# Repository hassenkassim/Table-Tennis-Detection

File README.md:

# Table-Tennis-Detection

> This project is about a detecting the impact position of table tennis ball on the racket by using 3 Piezo vibration sensors fixed to a table tennis racket and a custom designed microcontroller circuit (EMF32 GG).

## Note

The data model cannot be published. Nevertheless the mechanics is apparent.

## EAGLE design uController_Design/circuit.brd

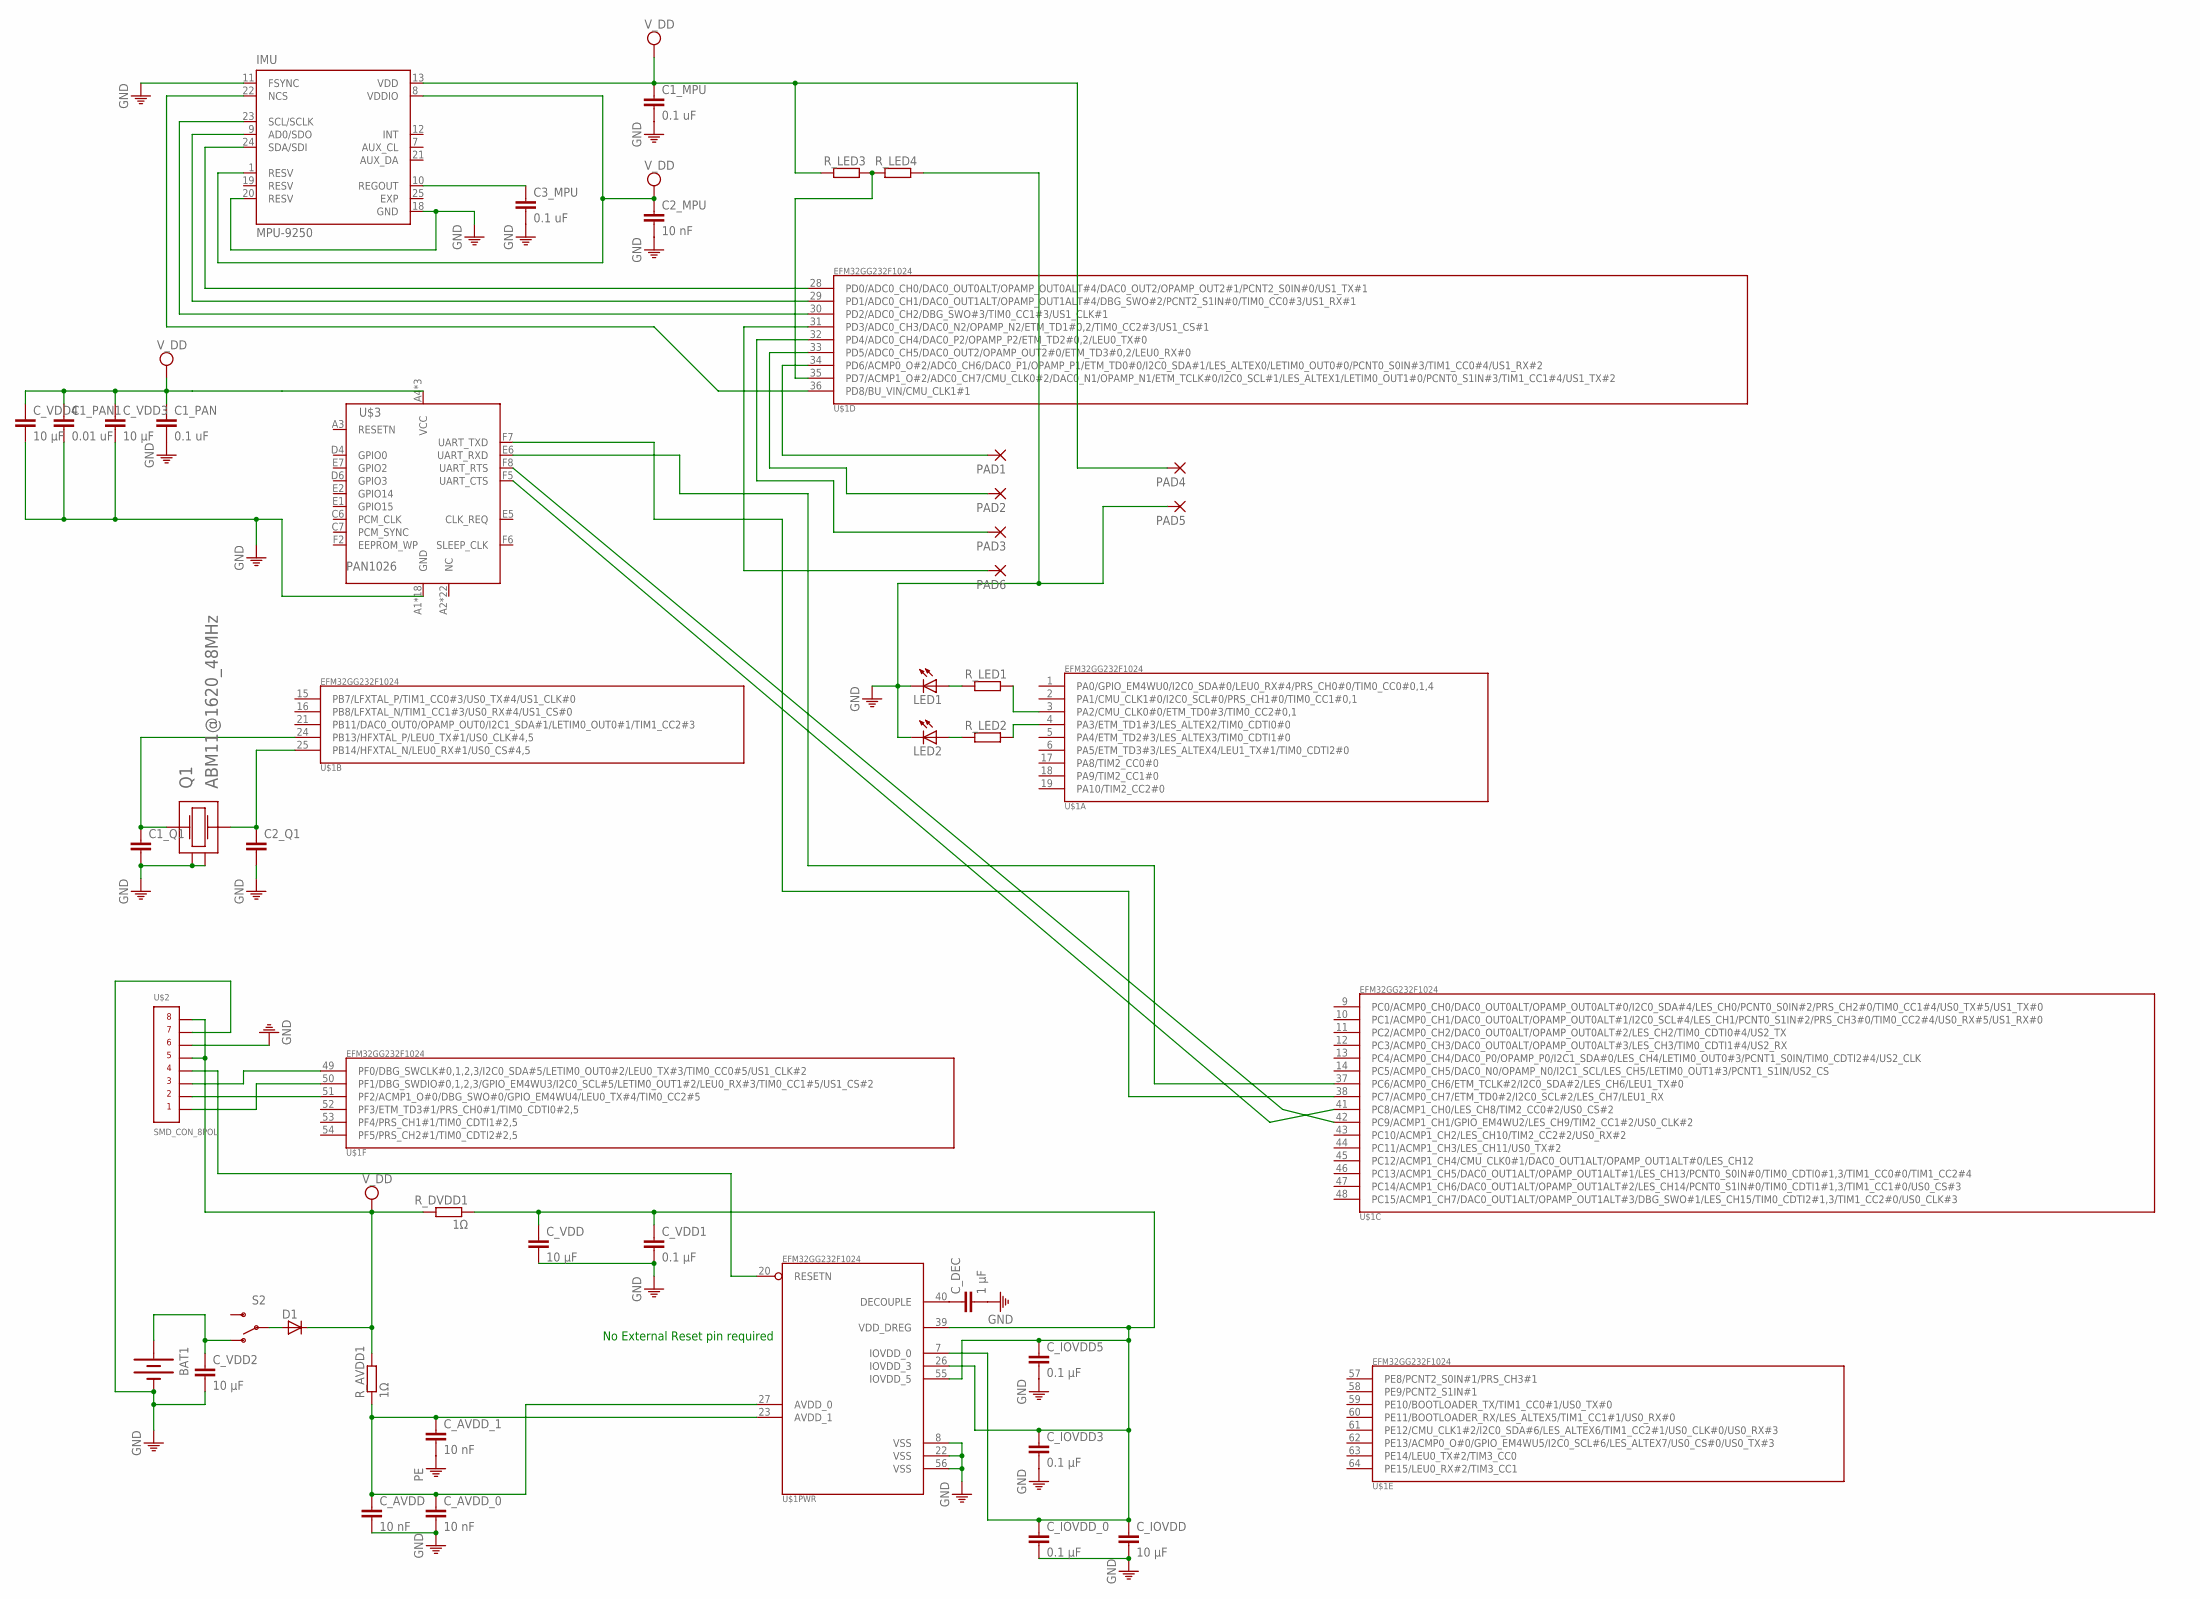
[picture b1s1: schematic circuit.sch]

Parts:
BAT1: BATTERY20MM_4LEGS_OVERPASTE; BATTCON_20MM_4LEGS_OVERPASTE
C1_MPU, C1_PAN, C3_MPU: 0.1 uF; C0603
C1_PAN1: 0.01 uF; C0603
C1_Q1, C2_Q1: C-EUC0603; C0603
C2_MPU: 10 nF; C0603
C_AVDD: 10 nF; C0603
C_AVDD_0, C_AVDD_1: 10 nF; C0603
C_DEC: 1 µF; C0603
C_IOVDD: 10 µF; C0805
C_IOVDD3, C_IOVDD5: 0.1 µF; C0603
C_IOVDD_0: 0.1 µF; C0603
C_VDD, C_VDD2, C_VDD3, C_VDD4: 10 µF; C0805
C_VDD1: 0.1 µF; C0603
D1: D-SOD123; SOD123
IMU: MPU-9250; QFN40P300X300X105-25N
LED1, LED2: LEDCHIPLED_0805; CHIPLED_0805
PAD1, PAD2, PAD3, PAD4, PAD5, PAD6: SMD2; SMD1,27-2,54
Q1: ABM11@1620_48MHz; 1620
R_AVDD1: 1Ω; R0603
R_DVDD1: 1Ω; R0603
R_LED1, R_LED2, R_LED3, R_LED4: R-EU_R0603; R0603
S2: SWITCH-SPDTSMD2; SWITCH-SPDT-SMD
U$1: EFM32GG232F1024; QFP64
U$2: SMD_CON_8POL
U$3: PAN1026

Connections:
EXP: IMU.25 (EXP)
GND: BAT1.2 (-), C1_MPU.2, C1_PAN.2, C1_PAN1.2, C1_Q1.2, C2_MPU.2, C2_Q1.2, C3_MPU.2, C_AVDD.2, C_AVDD_0.2, C_AVDD_1.2, C_DEC.2, C_IOVDD.2, C_IOVDD3.2, C_IOVDD5.2, C_IOVDD_0.2, C_VDD.2, C_VDD1.2, C_VDD2.2, C_VDD3.2, C_VDD4.2, IMU.11 (FSYNC), IMU.18 (GND), IMU.20 (RESV), LED1.C, LED2.C, PAD5.1, Q1.P$2, Q1.P$4, R_LED4.1, U$1.8 (VSS), U$1.22 (VSS), U$1.56 (VSS), U$2.P$6 (6), U$2.P$7, U$3.A1 (GND), U$3.A7 (GND), U$3.A9 (GND), U$3.A11 (GND), U$3.A12 (GND), U$3.C8 (GND), U$3.C9 (GND), U$3.D7 (GND), U$3.D8 (GND), U$3.E3 (GND), U$3.E8 (GND), U$3.E9 (GND), U$3.F1 (GND), U$3.F3 (GND), U$3.F4 (GND), U$3.F9 (GND), U$3.F11 (GND), U$3.F12 (GND)
unnamed: C_DEC.1, U$1.40 (DECOUPLE)
unnamed: C_IOVDD.1, C_IOVDD3.1, C_IOVDD5.1, C_IOVDD_0.1, C_VDD.1, C_VDD1.1, R_DVDD1.1, U$1.7 (IOVDD_0), U$1.26 (IOVDD_3), U$1.39 (VDD_DREG), U$1.55 (IOVDD_5)
unnamed: PAD3.1, U$1.32 (PD4/ADC0_CH4/DAC0_P2/OPAMP_P2/ETM_TD2#0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)
unnamed: C2_Q1.1, Q1.P$1, U$1.25 (PB14/HFXTAL_N/LEU0_RX#1/US0_CS#4,5)
unnamed: C_AVDD.1, C_AVDD_0.1, C_AVDD_1.1, R_AVDD1.1, U$1.23 (AVDD_1), U$1.27 (AVDD_0)
unnamed: BAT1.1 (+), C_VDD2.1, S2.1 (O)
unnamed: PAD2.1, U$1.33 (PD5/ADC0_CH5/DAC0_OUT2/OPAMP_OUT2#0/ETM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)
unnamed: C1_Q1.1, Q1.P$3, U$1.24 (PB13/HFXTAL_P/LEU0_TX#1/US0_CLK#4,5)
unnamed: U$1.50 (PF1/DBG_SWDIO#0,1,2,3/GPIO_EM4WU3/I2C0_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), U$2.P$1 (1)
unnamed: U$1.51 (PF2/ACMP1_O#0/DBG_SWO#0/GPIO_EM4WU4/LEU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), U$2.P$2 (2)
unnamed: D1.2 (A), S2.2
unnamed: U$1.20 (RESETN), U$2.P$4 (4)
unnamed: IMU.22 (NCS), U$1.36 (PD8/BU_VIN/CMU_CLK1#1)
unnamed: IMU.23 (SCL/SCLK), U$1.30 (PD2/ADC0_CH2/DBG_SWO#3/TIM0_CC1#3/US1_C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)
unnamed: IMU.9 (AD0/SDO), U$1.29 (PD1/ADC0_CH1/DAC0_OUT1ALT/OPAMP_OUT1ALT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)
unnamed: IMU.24 (SDA/SDI), U$1.28 (PD0/ADC0_CH0/DAC0_OUT0ALT/OPAMP_OUT0ALT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)
unnamed: C3_MPU.1, IMU.10 (REGOUT)
unnamed: LED1.A, R_LED1.2
unnamed: LED2.A, R_LED2.2
unnamed: R_LED1.1, U$1.3 (PA2/CMU_CLK0#0/ETM_TD0#3/TIM0_CC2#0,1)
unnamed: R_LED2.1, U$1.4 (PA3/ETM_TD1#3/LES_ALTEX2/TIM0_CDTI0#0)
unnamed: PAD1.1, U$1.34 (PD6/ACMP0_O#2/ADC0_CH6/DAC0_P1/OPAMP_P1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)
unnamed: PAD6.1, U$1.31 (PD3/ADC0_CH3/DAC0_N2/OPAMP_N2/ETM_TD1#0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)
unnamed: U$1.37 (PC6/ACMP0_CH6/ETM_TCLK#2/I2C0_SDA#2/LES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), U$3.E6 (UART_RXD)
unnamed: U$1.38 (PC7/ACMP0_CH7/ETM_TD0#2/I2C0_SCL#2/LES_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), U$3.F7 (UART_TXD)
unnamed: U$1.49 (PF0/DBG_SWCLK#0,1,2,3/I2C0_SDA#5/LETIM0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), U$2.P$3 (3)
unnamed: R_LED3.1, R_LED4.2, U$1.35 (PD7/ACMP1_O#2/ADC0_CH7/CMU_CLK0#2/DAC0_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)
unnamed: U$1.42 (PC9/ACMP1_CH1/GPIO_EM4WU2/LES_CH9/TIM2_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), U$3.F8 (UART_RTS)
unnamed: U$1.41 (PC8/ACMP1_CH0/LES_CH8/TIM2_CC0#2/US0_CS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), U$3.F5 (UART_CTS)
RESV: IMU.19 (RESV)
VDD: C1_MPU.1, C1_PAN.1, C1_PAN1.1, C2_MPU.1, C_VDD3.1, C_VDD4.1, D1.1 (C), IMU.1 (RESV), IMU.8 (VDDIO), IMU.13 (VDD), PAD4.1, R_AVDD1.2, R_DVDD1.2, R_LED3.2, U$2.P$5 (5), U$2.P$8, U$3.A4 (VCC), U$3.A5 (VCC), U$3.A6 (VCC)

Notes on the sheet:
No External Reset pin required

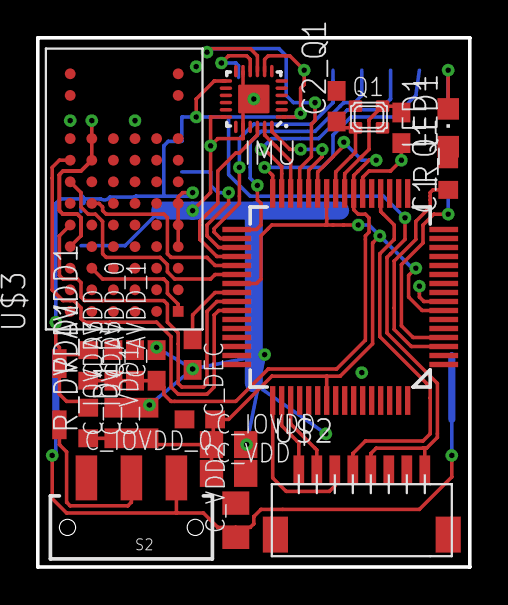
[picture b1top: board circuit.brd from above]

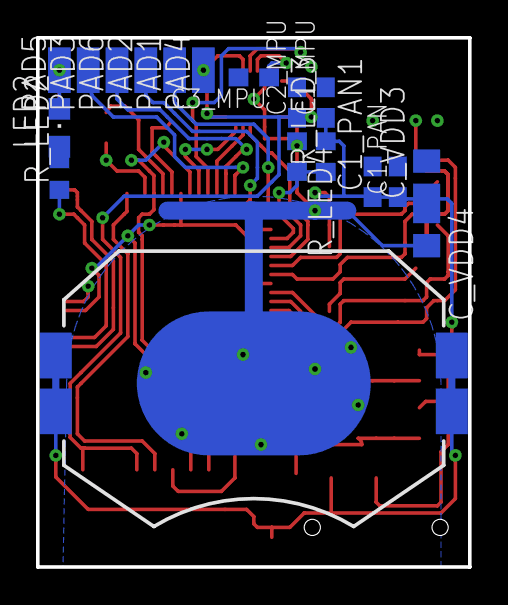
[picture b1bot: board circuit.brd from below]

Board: 2 copper layers, 24.0 x 29.4 mm, 42 parts (18 on the bottom side), 31 nets.

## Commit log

2017-06-21 Upload
    Upload files
2017-06-21 Set theme jekyll-theme-cayman

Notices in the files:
parts and their libraries:
SparkFun-Electromechanical: Licensing: Creative Commons ShareAlike 4.0 International - https://creativecommons.org/licenses/by-sa/4.0
EnergyMicro: CC0 License
